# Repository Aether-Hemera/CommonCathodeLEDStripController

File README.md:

CommonCathodeLEDStripController
===============================

Arduino shield for a series of Common Cathode LED Strips 

====

Release 1 - 2012 09 04

This is the first release of the board.
Terminals are not close to each other and it's crammed.
But the benefit is that it's within the boundaries of Eagles's free license.

Enjoy

Aether@aether-hemera.com

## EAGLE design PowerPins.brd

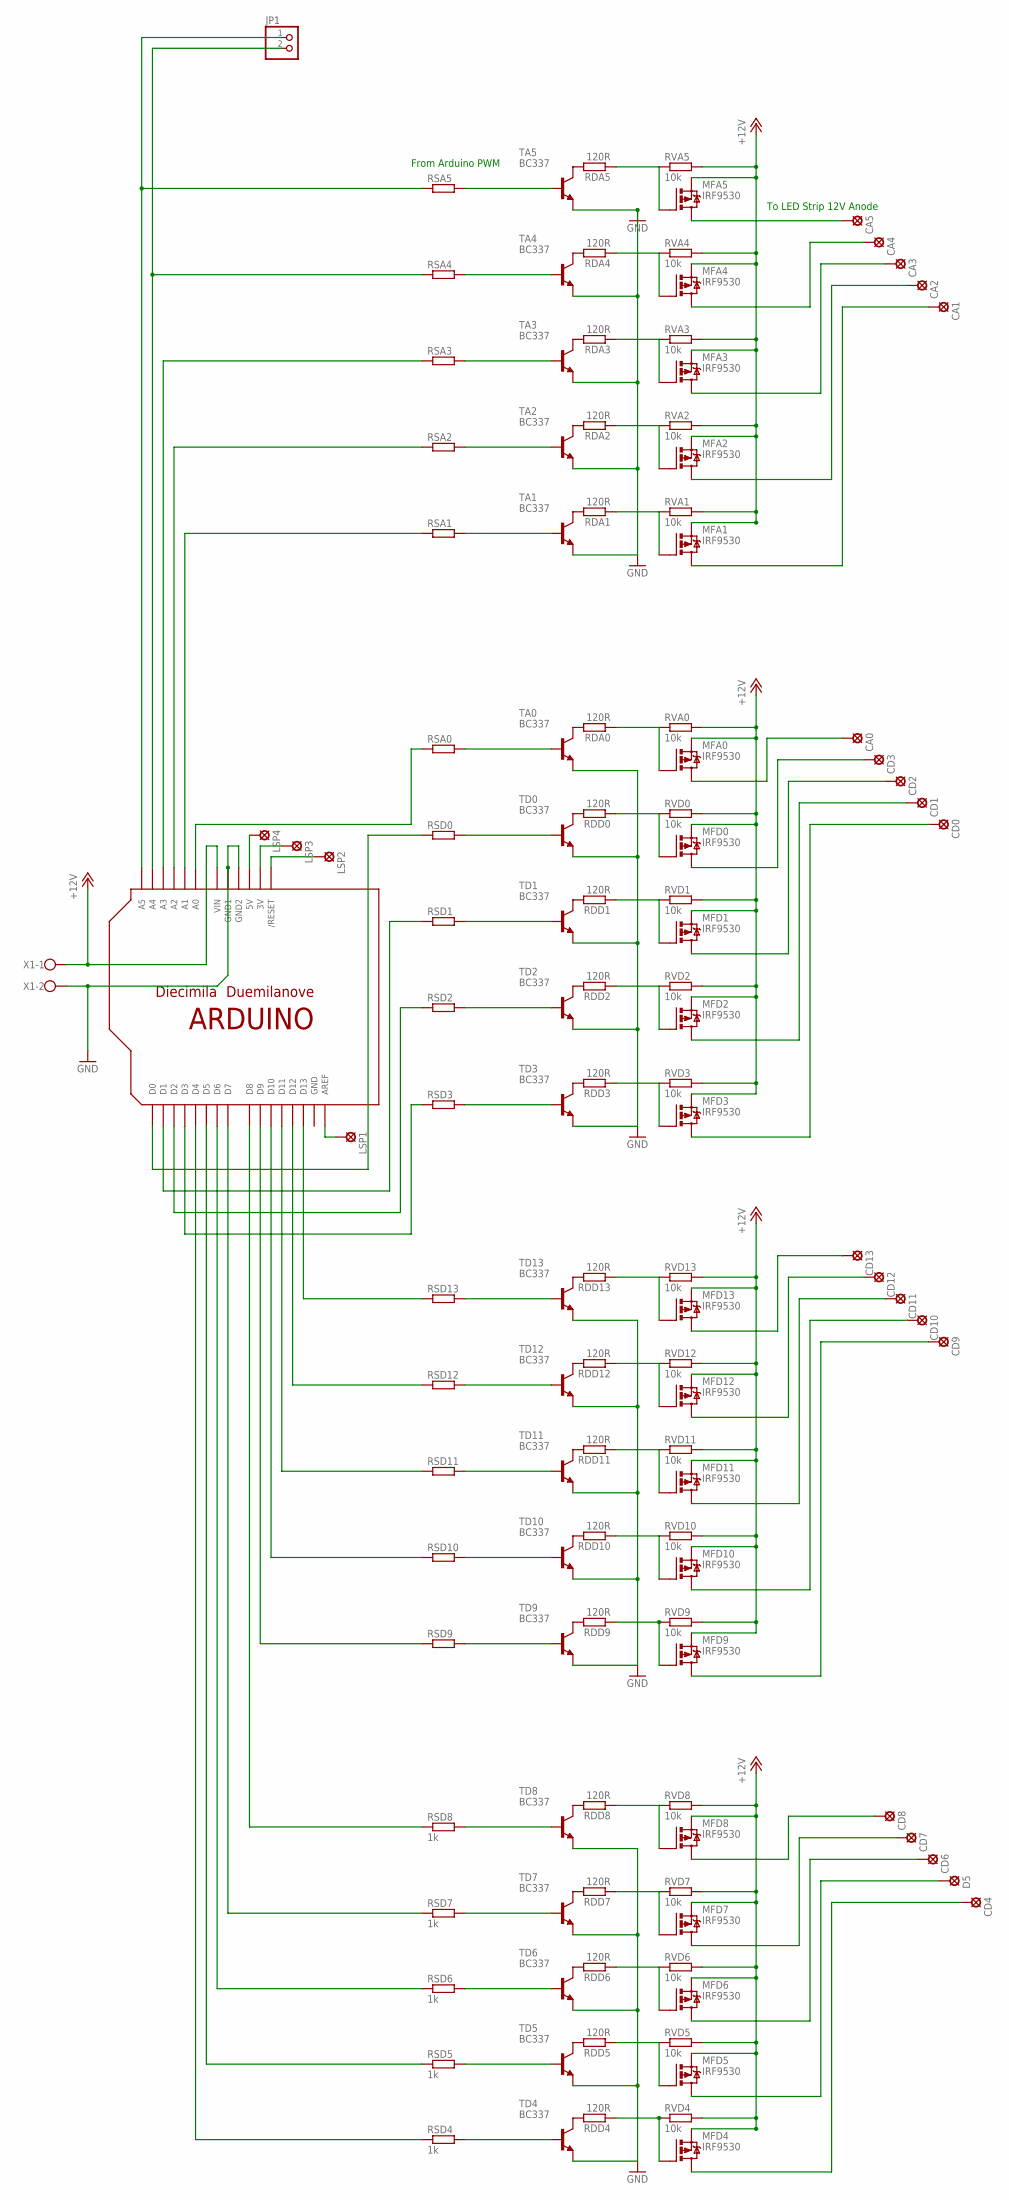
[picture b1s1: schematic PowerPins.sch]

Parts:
CA0, CA1, CA2, CA3, CA4, CA5: SE14
CD0, CD1, CD2, CD3, CD4, CD6, CD7, CD8, CD9, CD10, CD11, CD12, CD13: SE14
D5: SE14
JP1: PINHD-1X2; 1X02
LSP1, LSP2, LSP3, LSP4: MCS10B
MFA0, MFA1, MFA2, MFA3, MFA4, MFA5: IRF9530; TO220BV
MFD0, MFD1, MFD2, MFD3, MFD4, MFD5, MFD6, MFD7, MFD8, MFD9, MFD10, MFD11, MFD12, MFD13: IRF9530; TO220BV
RDA0, RDA1, RDA2, RDA3, RDA4, RDA5: 120R; 0204/5
RDD0, RDD1, RDD2, RDD3, RDD4, RDD5, RDD6, RDD7, RDD8, RDD9, RDD10, RDD11, RDD12, RDD13: 120R; 0204/5
RSA0, RSA1, RSA2, RSA3, RSA4, RSA5: R-EU_0204/5; 0204/5
RSD0, RSD1, RSD2, RSD3, RSD9, RSD10, RSD11, RSD12, RSD13: R-EU_0204/5; 0204/5
RSD4, RSD5, RSD6, RSD7, RSD8: 1k; 0204/5
RVA0, RVA1, RVA2, RVA3, RVA4, RVA5: 10k; 0204/5
RVD0, RVD1, RVD2, RVD3, RVD4, RVD5, RVD6, RVD7, RVD8, RVD9, RVD10, RVD11, RVD12, RVD13: 10k; 0204/5
TA0, TA1, TA2, TA3, TA4, TA5: BC337; TO92
TD0, TD1, TD2, TD3, TD4, TD5, TD6, TD7, TD8, TD9, TD10, TD11, TD12, TD13: BC337; TO92
U$1: ARDUINOUNO; ARDUINO
X1: W237-102

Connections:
+12V: MFA0.S, MFA1.S, MFA2.S, MFA3.S, MFA4.S, MFA5.S, MFD0.S, MFD1.S, MFD2.S, MFD3.S, MFD4.S, MFD5.S, MFD6.S, MFD7.S, MFD8.S, MFD9.S, MFD10.S, MFD11.S, MFD12.S, MFD13.S, RVA0.2, RVA1.2, RVA2.2, RVA3.2, RVA4.2, RVA5.2, RVD0.2, RVD1.2, RVD2.2, RVD3.2, RVD4.2, RVD5.2, RVD6.2, RVD7.2, RVD8.2, RVD9.2, RVD10.2, RVD11.2, RVD12.2, RVD13.2, U$1.VIN, X1.1
C9V: RSA0.1, U$1.A0
CD12: CD11.MP, MFD11.D
CD13: CD12.MP, MFD12.D
GND: TA0.1 (E), TA1.1 (E), TA2.1 (E), TA3.1 (E), TA4.1 (E), TA5.1 (E), TD0.1 (E), TD1.1 (E), TD2.1 (E), TD3.1 (E), TD4.1 (E), TD5.1 (E), TD6.1 (E), TD7.1 (E), TD8.1 (E), TD9.1 (E), TD10.1 (E), TD11.1 (E), TD12.1 (E), TD13.1 (E), U$1.GND, U$1.GND1, U$1.GND2, X1.2
MFD9: CD9.MP, MFD9.D
MFDA3: CA3.MP, MFA3.D
unnamed: RDA5.2, TA5.3 (C)
unnamed: RSA5.2, TA5.2 (B)
unnamed: MFA5.G, RDA5.1, RVA5.1
unnamed: RDA4.2, TA4.3 (C)
unnamed: RSA4.2, TA4.2 (B)
unnamed: RDA0.2, TA0.3 (C)
unnamed: RSA0.2, TA0.2 (B)
unnamed: MFA0.G, RDA0.1, RVA0.1
unnamed: RDD0.2, TD0.3 (C)
unnamed: RSD0.2, TD0.2 (B)
unnamed: RDD10.2, TD10.3 (C)
unnamed: RSD10.2, TD10.2 (B)
unnamed: MFD10.G, RDD10.1, RVD10.1
unnamed: RDA1.2, TA1.3 (C)
unnamed: CA5.MP, MFA5.D
unnamed: RDD8.2, TD8.3 (C)
unnamed: RSD8.2, TD8.2 (B)
unnamed: MFD8.G, RDD8.1, RVD8.1
unnamed: RDD7.2, TD7.3 (C)
unnamed: RDD4.2, TD4.3 (C)
unnamed: LSP4.MP, U$1.5V
unnamed: RSA1.1, U$1.A1
unnamed: RSA2.1, U$1.A2
unnamed: RSA3.1, U$1.A3
unnamed: JP1.2, RSA4.1, U$1.A4
unnamed: JP1.1, RSA5.1, U$1.A5
unnamed: CA4.MP, MFA4.D
unnamed: RSD13.1, U$1.D13
unnamed: RSD12.1, U$1.D12
unnamed: RSD11.1, U$1.D11
unnamed: CA2.MP, MFA2.D
unnamed: RSD10.1, U$1.D10
unnamed: RSD9.1, U$1.D9
unnamed: RSD8.1, U$1.D8
unnamed: RSD7.1, U$1.D7
unnamed: CA1.MP, MFA1.D
unnamed: RSD6.1, U$1.D6
unnamed: CA0.MP, MFA0.D
unnamed: CD3.MP, MFD0.D
unnamed: RSD5.1, U$1.D5
unnamed: CD2.MP, MFD1.D
unnamed: CD1.MP, MFD2.D
unnamed: CD0.MP, MFD3.D
unnamed: CD13.MP, MFD13.D
unnamed: RSA1.2, TA1.2 (B)
unnamed: MFA1.G, RDA1.1, RVA1.1
unnamed: CD10.MP, MFD10.D
unnamed: RDD11.2, TD11.3 (C)
unnamed: CD8.MP, MFD8.D
unnamed: CD7.MP, MFD7.D
unnamed: CD6.MP, MFD6.D
unnamed: LSP3.MP, U$1.3V
unnamed: D5.MP, MFD5.D
unnamed: CD4.MP, MFD4.D
unnamed: RSD4.1, U$1.D4
unnamed: RSD3.1, U$1.D3
unnamed: RSD2.1, U$1.D2
unnamed: LSP2.MP, U$1.RESET (/RESET)
unnamed: LSP1.MP, U$1.AREF
unnamed: RSD4.2, TD4.2 (B)
unnamed: RDD9.2, TD9.3 (C)
unnamed: RSD11.2, TD11.2 (B)
unnamed: MFD9.G, RDD9.1, RVD9.1
unnamed: MFD4.G, RDD4.1, RVD4.1
unnamed: MFD11.G, RDD11.1, RVD11.1
unnamed: RDD12.2, TD12.3 (C)
unnamed: RSD12.2, TD12.2 (B)
unnamed: MFD12.G, RDD12.1, RVD12.1
unnamed: RDD13.2, TD13.3 (C)
unnamed: RSD13.2, TD13.2 (B)
unnamed: MFD13.G, RDD13.1, RVD13.1
unnamed: RSD7.2, TD7.2 (B)
unnamed: MFD7.G, RDD7.1, RVD7.1
unnamed: RDD6.2, TD6.3 (C)
unnamed: RSD6.2, TD6.2 (B)
unnamed: MFD6.G, RDD6.1, RVD6.1
unnamed: RDD5.2, TD5.3 (C)
unnamed: RSD5.2, TD5.2 (B)
unnamed: MFD5.G, RDD5.1, RVD5.1
unnamed: MFD0.G, RDD0.1, RVD0.1
unnamed: RDD1.2, TD1.3 (C)
unnamed: RSD1.2, TD1.2 (B)
unnamed: MFD1.G, RDD1.1, RVD1.1
unnamed: RDD2.2, TD2.3 (C)
unnamed: RSD2.2, TD2.2 (B)
unnamed: MFD2.G, RDD2.1, RVD2.1
unnamed: RDD3.2, TD3.3 (C)
unnamed: RSD3.2, TD3.2 (B)
unnamed: MFD3.G, RDD3.1, RVD3.1
unnamed: MFA4.G, RDA4.1, RVA4.1
unnamed: RDA3.2, TA3.3 (C)
unnamed: RSA3.2, TA3.2 (B)
unnamed: MFA3.G, RDA3.1, RVA3.1
unnamed: RDA2.2, TA2.3 (C)
unnamed: RSA2.2, TA2.2 (B)
unnamed: MFA2.G, RDA2.1, RVA2.1
OUT0: RSD0.1, U$1.D0
OUT1: RSD1.1, U$1.D1
TD9: RSD9.2, TD9.2 (B)

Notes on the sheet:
From Arduino PWM
To LED Strip 12V Anode

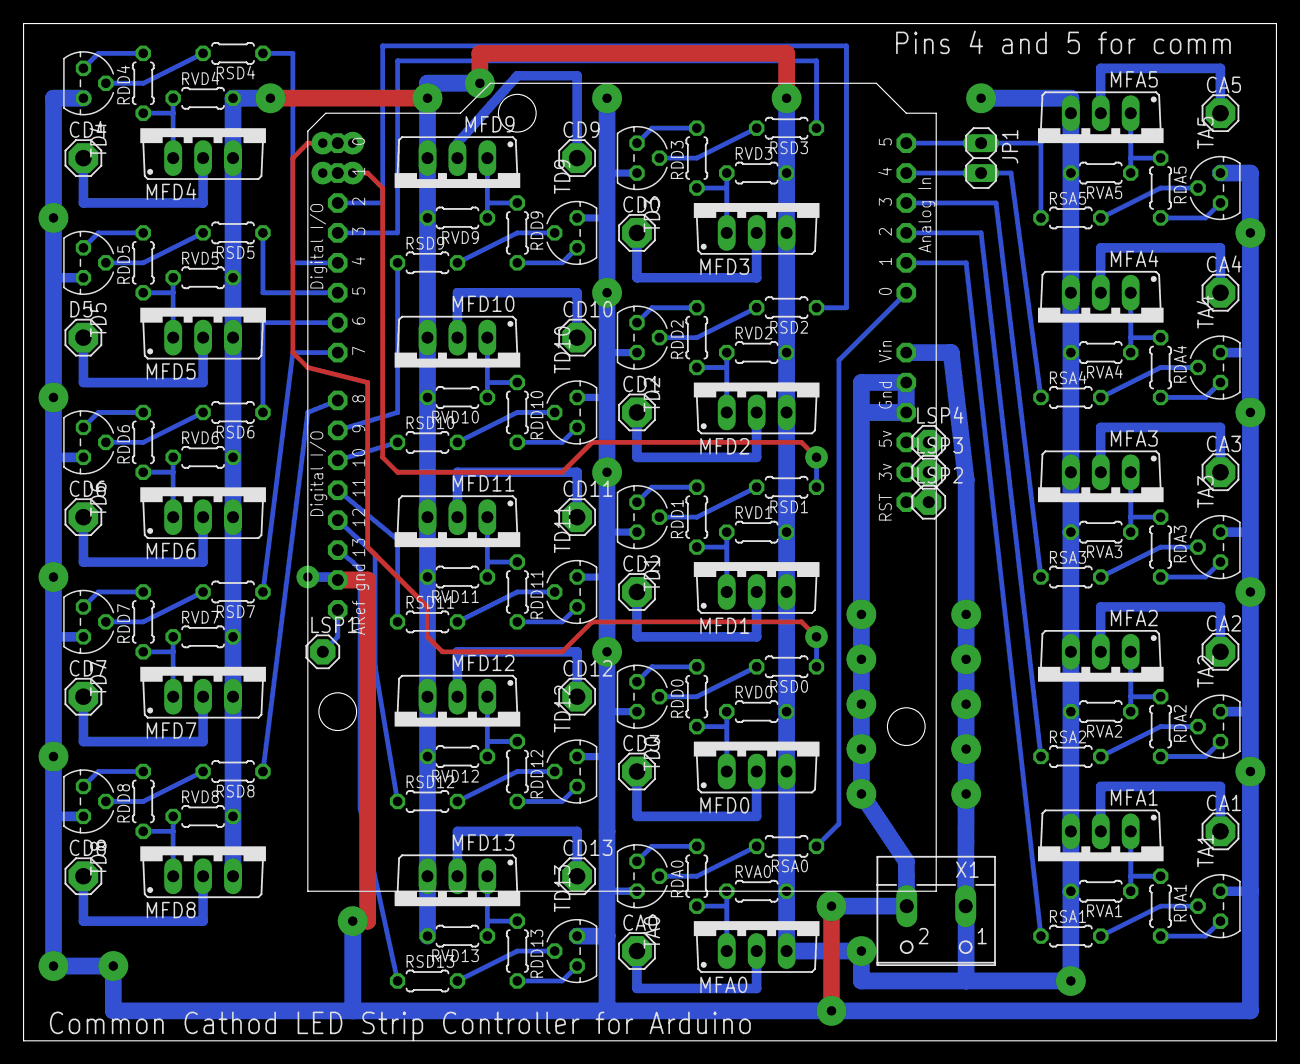
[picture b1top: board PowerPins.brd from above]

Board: 2 copper layers, 106.3 x 86.4 mm, 127 parts (0 on the bottom side), 106 nets.

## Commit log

2012-09-04 First version. Terminals are not close to each other and the board is crammed. But the benefit is that it's within the boundaries of Eagles's free license.
